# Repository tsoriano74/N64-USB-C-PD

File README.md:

# N64 USB-C Power Delivery 🔌

Salut les bidouilleurs et les makers !

J’ai travaillé sur ce petit PCB à la base pour mon projet de Nintendo 64 custom : l’idée était de pouvoir alimenter la console en USB-C, avec du **12 V, du 5 V et du 3,3 V** disponibles sur la carte. Je partage ici les fichiers KiCad et les fichiers de fabrication pour que vous puissiez regarder comment c’est fait et vous en inspirer pour vos propres bidouilles.

Le PCB a été retravaillé à partir des travaux de **Xenii2026** et de **CrazyGadget**, notamment le **PSU-PLUS**. Merci à eux pour les bases du projet !

## Comment ça fonctionne ?

Le principe : utiliser un chargeur **USB-C Power Delivery compatible avec un profil 12 V**. Le contrôleur **CH224K** s’occupe de la négociation avec le chargeur, puis deux convertisseurs **AP62301Z6-7** abaissent cette tension pour obtenir le 5 V et le 3,3 V.

```text
Chargeur USB-C PD compatible 12 V
              │
       CH224K : négociation
              │
             12 V ───────────────► sortie 12 V
              ├── AP62301 ───────► sortie 5 V
              └── AP62301 ───────► sortie 3,3 V
```

Le 12 V vient donc du chargeur après négociation ; le 5 V et le 3,3 V sont générés sur le PCB. Un chargeur USB-C ne propose pas forcément le profil 12 V : pensez à vérifier le vôtre.

La N64 a été le point de départ, mais ces trois tensions peuvent aussi donner des idées pour d’autres projets de makers. À vous de vérifier que les besoins de votre montage correspondent aux capacités de la carte.

## La carte en images

La carte assemblée, côté pastilles de raccordement :

Et côté USB-C :

### Rendu et routage

### Schéma complet

[Ouvrir le schéma en SVG](docs/images/schema-complet-noir.svg)

## Ce que vous trouverez ici

| Fichier ou dossier | À quoi ça sert |
|---|---|
| `hardware/` | Le projet KiCad, le schéma et le PCB pour explorer ou modifier la carte |
| `production/JLCPCBv2.zip` | Les Gerbers et les fichiers de perçage |
| `production/JLCPCBv2_bom.csv` | La BOM par carte, avec les références LCSC |
| `production/bom.xls` | La BOM Excel source fournie pour la commande |
| `production/JLCPCBv2_positions.csv` | Les positions et rotations des composants |
| `docs/images/N64-PSU.svg` | Le schéma consultable directement |
| `docs/PCB-INVENTORY.md` | Les composants et les connexions du PCB |
| `docs/VALIDATION.md` | Les vérifications et les points à compléter |
| `SOURCE-SHA256.txt` | Les empreintes de contrôle des sources et fichiers de production |

[Voir le schéma](docs/images/N64-PSU.svg) · [Voir les points à vérifier](docs/VALIDATION.md)

## Envie de mettre les mains dedans ?

Ouvrez `hardware/N64-PSU.kicad_pro` avec **KiCad 10**. Le PCB est en deux couches, avec une épaisseur déclarée de **1,6 mm**. Certaines bibliothèques personnelles et certains modèles 3D externes ne sont pas inclus ; les détails sont dans la documentation.

Quelques repères pour vous y retrouver :

- **J1** : entrée USB-C.
- **U3** : contrôleur CH224K.
- **U1 + L1** : conversion vers le 3,3 V, accessible sur **TP3**.
- **U2 + L2** : conversion vers le 5 V, accessible sur **TP5**.
- **TP4 et TP6** : masse.

## Avant de commander ou de brancher

La BOM contient **23 composants par carte**, avec les **références LCSC renseignées** à partir du fichier fourni le 23 novembre 2026. Utilisez [JLCPCBv2_bom.csv](production/JLCPCBv2_bom.csv) pour l’assemblage. Le [fichier Excel source](production/bom.xls) est aussi disponible : sa colonne Qty correspond aux quantités de commande, pas aux quantités à monter sur une seule carte.

### Le message « composants manquants » pour TP3 à TP6

Si JLCPCB indique que **TP3, TP4, TP5 et TP6 n’existent pas dans la BOM**, c’est normal : ce sont les **pastilles de test ou de soudure**, pas des composants à acheter et à assembler. Elles sont présentes dans le fichier de placement, mais volontairement absentes de la nomenclature. Vous pouvez continuer si le message concerne uniquement ces quatre repères. Si d’autres composants sont signalés, vérifiez leur correspondance.

### Vérifiez bien le sens des composants !

Dans l’aperçu d’assemblage JLCPCB, contrôlez que le **repère violet d’orientation** correspond au repère de la broche 1 sur la sérigraphie du PCB. Sur ma commande, **U1 et U2 ont nécessité une correction de rotation dans l’aperçu**. Comparez avec l’image ci-dessous avant de valider, et contrôlez aussi les autres composants orientés.

Cette capture sert de référence visuelle. Les rotations du fichier de placement fourni n’ont pas été modifiées : le sens doit être vérifié dans l’aperçu du fabricant, sans appliquer un angle au hasard.

Prenez le temps de contrôler les pièces choisies, les rotations et la cohérence des fichiers de fabrication avec votre version du PCB. Avant de brancher une console, mesurez les tensions et vérifiez le câblage. Les courants disponibles et les résultats thermiques ne sont pas encore documentés ici.

Les remarques techniques et les contrôles du projet sont regroupés dans [VALIDATION.md](docs/VALIDATION.md).

## Crédits et partage

Ce projet s’appuie sur le travail de **Xenii2026** et de **CrazyGadget / PSU-PLUS**. La sérigraphie conserve la mention « Based on CrazyGadget’s PSU-PLUS And Xenii 2026 ».

Si vous repérez une amélioration, adaptez la carte à un autre montage ou avez des retours de fabrication, venez les partager dans les issues ! C’est aussi comme ça qu’on fait avancer les projets entre makers.

Aucune licence de redistribution n’est définie pour le moment ; les licences des projets d’origine restent à vérifier avant d’en choisir une. Projet indépendant, sans affiliation avec Nintendo.

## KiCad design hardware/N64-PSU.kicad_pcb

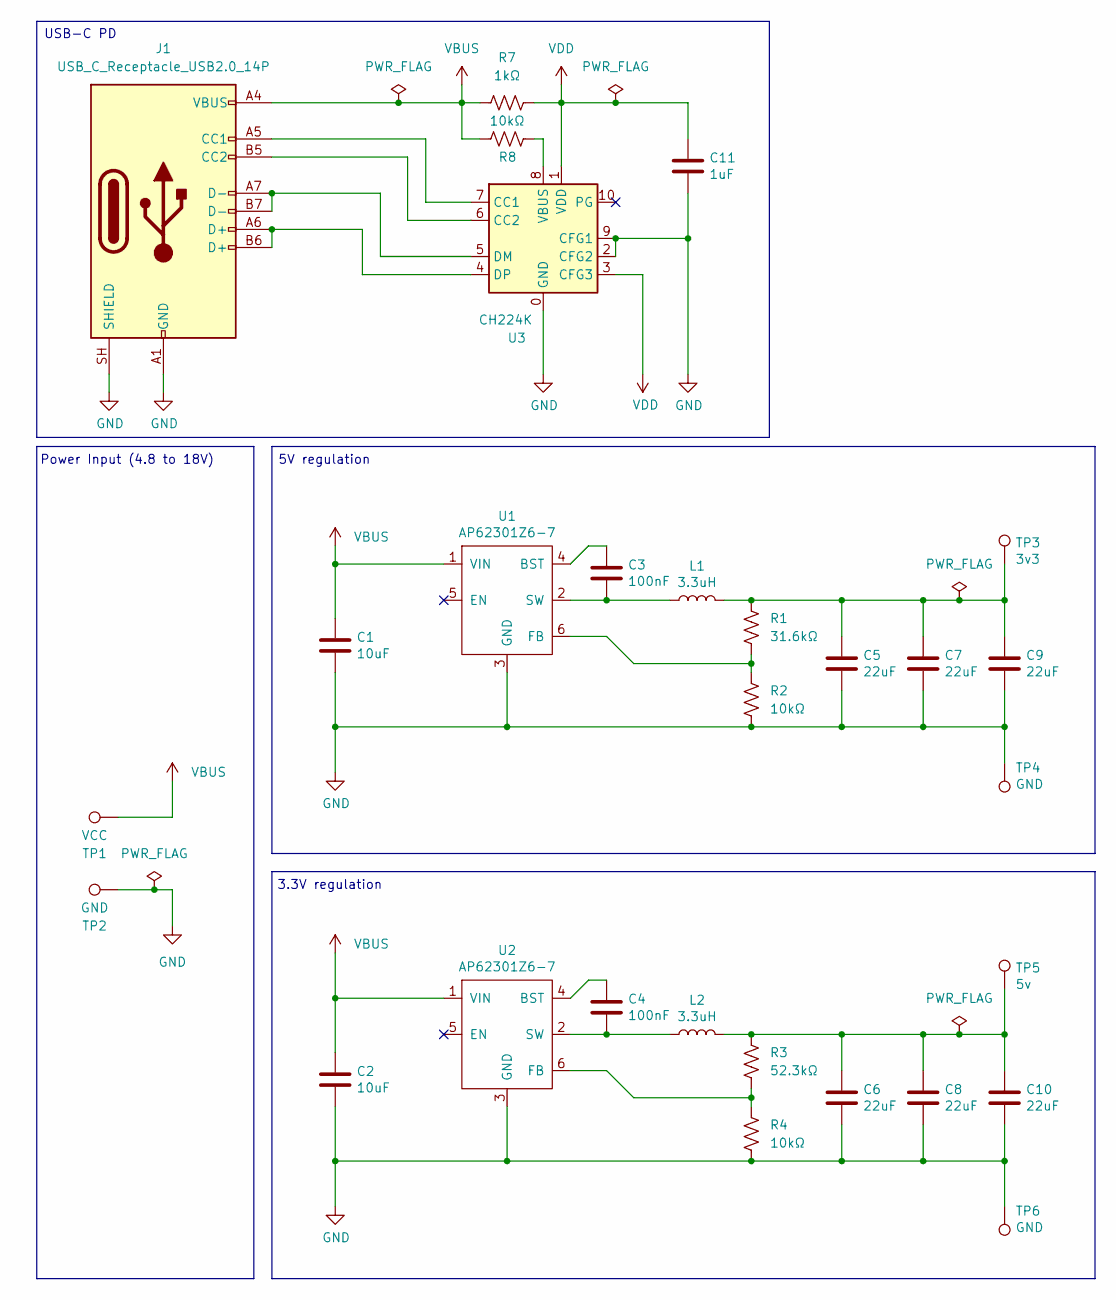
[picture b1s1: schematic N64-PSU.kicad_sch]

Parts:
C1, C2: 10uF; C_1206_3216Metric; JLCPCB C14860
C3, C4: 100nF; C_0402_1005Metric; JLCPCB C307331
C5, C6, C7, C8, C9, C10: 22uF; C_0603_1608Metric; JLCPCB C86295
C11: 1uF; C_0603_1608Metric; JLCPCB C29936
J1: USB_C_Receptacle_USB2.0_14P; USB_C_Receptacle_HRO_TYPE-C-31-M-12; JLCPCB C165948
L1, L2: 3.3uH; JLCPCB_L_Taiyo-Yuden_MD-5050; JLCPCB C5307606
R1: 31.6kΩ; R_0603_1608Metric_Pad0.98x0.95mm_HandSolder; JLCPCB C25967
R2, R4, R8: 10kΩ; R_0402_1005Metric; JLCPCB C25744
R3: 52.3kΩ; R_0603_1608Metric_Pad0.98x0.95mm_HandSolder; JLCPCB C23198
R7: 1kΩ; R_0402_1005Metric; JLCPCB C11702
TP1: VCC; PowerPad
TP2: GND; PowerPad
TP3: 3v3; TestPoint_Pad_2.0x2.0mm
TP4, TP6: GND; TestPoint_Pad_2.0x2.0mm
TP5: 5v; TestPoint_Pad_2.0x2.0mm
U1, U2: AP62301Z6-7; SOT-563; JLCPCB C1880992
U3: CH224K; SSOP-10-1EP_3.9x4.9mm_P1mm_EP2.1x3.3mm; JLCPCB C970725

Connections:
GND: C1.1, C2.1, C5.2, C6.2, C7.2, C8.2, C9.2, C10.2, C11.2, J1.A1 (GND), J1.A12 (GND), J1.B1 (GND), J1.B12 (GND), J1.SH (SHIELD), R2.2, R4.2, TP2.1, TP4.1 (1_1), TP6.1 (1_1), U1.3 (GND), U2.3 (GND), U3.0 (GND), U3.2 (CFG2), U3.9 (CFG1)
unnamed: C5.1, C7.1, C9.1, L1.2, R1.1, TP3.1 (1_1)
unnamed: C6.1, C8.1, C10.1, L2.2, R3.1, TP5.1 (1_1)
unnamed: J1.A5 (CC1), U3.7 (CC1)
unnamed: J1.B5 (CC2), U3.6 (CC2)
unnamed: C3.1, U1.4 (BST)
unnamed: R1.2, R2.1, U1.6 (FB)
unnamed: C3.2, L1.1, U1.2 (SW)
unnamed: C4.1, U2.4 (BST)
unnamed: R3.2, R4.1, U2.6 (FB)
unnamed: C4.2, L2.1, U2.2 (SW)
unnamed: J1.A7 (D-), J1.B7 (D-), U3.5 (DM)
unnamed: J1.A6 (D+), J1.B6 (D+), U3.4 (DP)
unnamed: R8.2, U3.8 (VBUS)
VBUS: C1.2, C2.2, J1.A4 (VBUS), J1.A9 (VBUS), J1.B4 (VBUS), J1.B9 (VBUS), R7.2, R8.1, TP1.1, U1.1 (VIN), U2.1 (VIN)
VDD: C11.1, R7.1, U3.1 (VDD), U3.3 (CFG3)

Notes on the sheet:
5V regulation
3.3V regulation
Power Input (4.8 to 18V)
USB-C PD

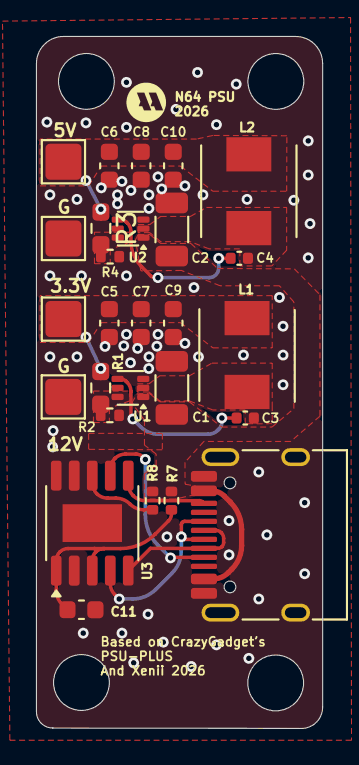
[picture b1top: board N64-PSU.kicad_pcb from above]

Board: 2 copper layers, 15.9 x 38.4 mm, 27 parts (0 on the bottom side), 16 nets.

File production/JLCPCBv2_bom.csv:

Designator,Footprint,Quantity,Value,LCSC Part #
"C1, C2",1206,2,10uF,
"C10, C5, C6, C7, C8, C9",0603,6,22uF,
C11,0603,1,1uF,
"C3, C4",0402,2,100nF,
J1,USB_C_Receptacle_HRO_TYPE-C-31-M-12,1,USB_C_Receptacle_USB2.0_14P,
"L1, L2",JLCPCB_L_Taiyo-Yuden_MD-5050,2,3.3uH,
R1,0603,1,31.6kΩ,
"R2, R4, R8",0402,3,10kΩ,
R3,0603,1,52.3kΩ,
R7,0402,1,1kΩ,
"U1, U2",SOT-563,2,AP62301Z6-7,
U3,SSOP-10-1EP_3.9x4.9mm_P1mm_EP2.1x3.3mm,1,CH224K,
